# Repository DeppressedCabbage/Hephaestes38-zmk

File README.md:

<h1 align="left">Hephaestes38</h1>

Hephaestes38 is a custom, 38 key, low profile, split unibody keyboard. I Intended it to be used with the Hands Down promethium layout, but that's really up to you! ZMK studio has also been integrated, so it's super easy to make any changes you wish. See the [writeup](https://github.com/DeppressedCabbage/Hephaestes38-zmk/blob/main/Keymap.md) on Hands Down Promethium and my specific combos/layers. I only use 3 Layers, but the firmware has a total of 5 for you to add any you like. 

****

It's programmed on a Nice!Nano for wireless functonality, as well as compatibility for a Nice!View E-paper display to keep track of layers, battery status, or whatever else suits your fancy.

***
### PCB's
All files to make your own pcb's can be found in the pcb's and cases folder. The Hepheaestes38_PCB-Gerbers.zip can be uploaded into any pcb manufacturer to get them made, and all of the kicad files are available if you want to make any edits. If you are looking for an assembled PCB, reach out to me at conturakeyboards@gmail.com. A website will be coming soon if you would like to purchase pcb's or fully assembled keyboards. Stay tuned. 

***
### BOM

Additionally, you'll also need the following

- 38x SMD diodes (1N4148W)
- 38x Kailh Choc Hotswap Sockets
- 38x Kailh Choc V1 Switches
- 1x Nice!Nano
- 2× Pair of headers and sockets for the N!N (I used the easy solder machine headers, but mil-max sockets will work just fine too)
- (optional) 1x Nice!View
- (optional) 1x Lipo battery (301230)
- (optional) 1x Power switch (PCM12)
- (optional) 1x Reset switch (PTS526)
- (optional) Rubber feet to stop the keyboard sliding around (I used 3mm by 10mm ones, but if you aren't using a case it shouldn't matter much)

***
### Firmware

Hepheaestes38 runs ZMK, you can modify and compile you're own firmware by cloning the repo and making any edits you like. 

*** 
### V1 Case

This is the first version of they keyboard, and I forgot to add mounting holes to the pcb to facilitate Case attachement. I worked around this in a less than elegant way, and if you want to make v1 you would have to do something similar. Pictures are below. 

### V2 Case

Version 2 of the pcb and case are currently in progress, please follow for updates coming soon. In the meantime, here are some renders for your viewing pleasure. 

***
### To Do List

- ✔Create Case
- ✔Add via's to the pcb to facilitate Case attachement
- ✔Refine Pcb to allow for diode attachment on both sides, along with turning Diode Footprint around
- Lower profile?
- ✔ Add zmk Studio support
- Order V2 pcb's to confirm fitment

***
### Credits

This is my first foray into making my own keyboard, so special thanks go out to the entire ergo community, notably 

- [FlatFootFox](https://twitter.com/flatfootfox) - for the guide to ergogen
- [Ceoloide](https://github.com/ceoloide) - For the footprints used in creating the pcb
- [Lesshonor](https://github.com/lesshonor) - For helping me out with the getting the display to work
- And my lovely offline support system for moral support and encouragement.

***

## LICENSING
<picture align="left">
  
</picture>

This work is licensed under a
Creative Commons (4.0 International License)
Attribution—Noncommercial—Share Alike

- ✖ | Sharing without ATTRIBUTION
- ✔ | Remix Culture allowed
- ✖ | Commercial Use
- ✖ | Free Cultural Works
- ✖ | Meets Open Definition

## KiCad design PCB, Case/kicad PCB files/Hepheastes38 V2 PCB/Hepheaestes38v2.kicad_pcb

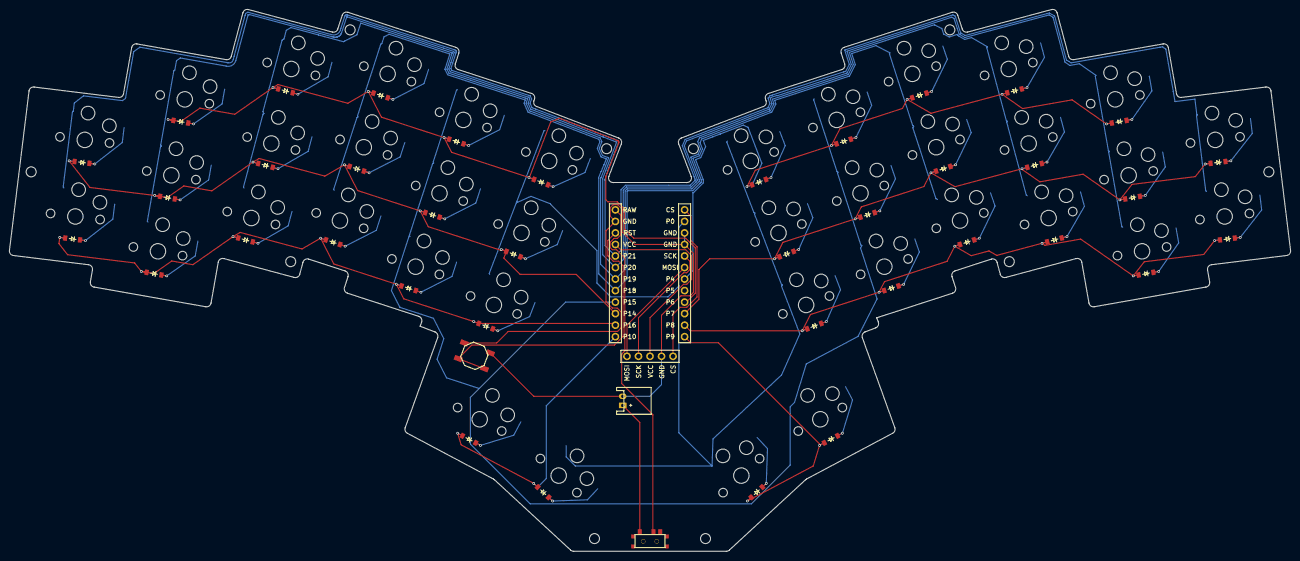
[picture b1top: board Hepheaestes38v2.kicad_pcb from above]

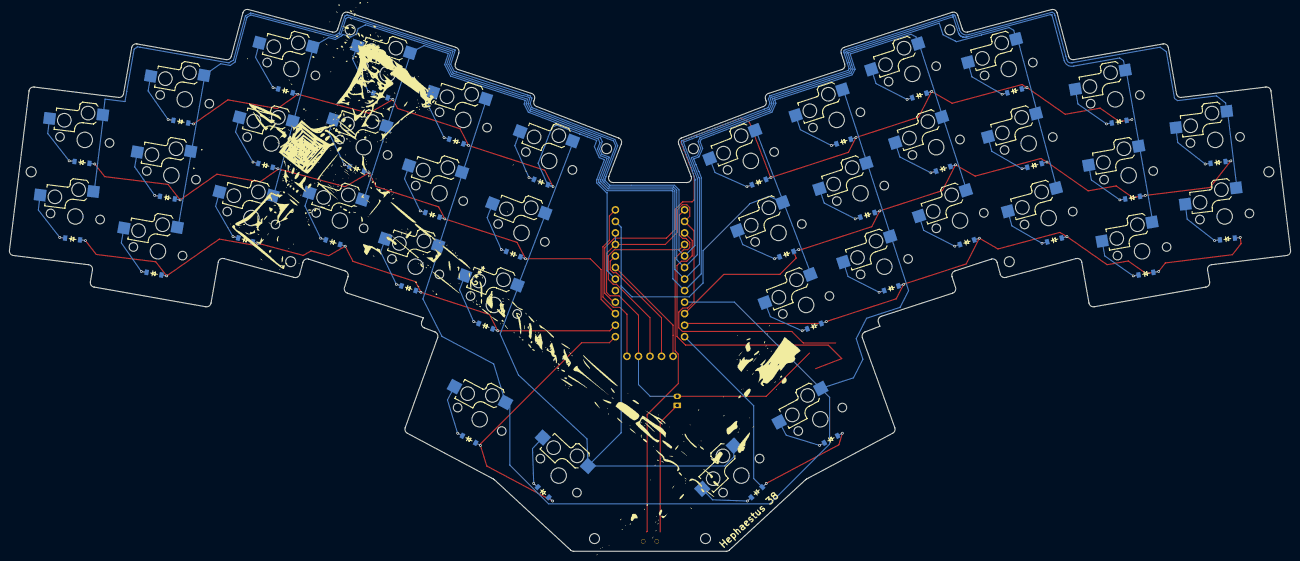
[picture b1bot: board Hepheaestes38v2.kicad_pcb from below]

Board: 2 copper layers, 282.3 x 119.4 mm, 91 parts (38 on the bottom side), 60 nets.

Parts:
B1: SW_TACT_ALPS_SKQGABE010
D1, D2, D3, D4, D5, D6, D7, D8, D9, D10, D11, D12, D13, D14, D15, D16, D17, D18, D19, D20, D21, D22, D23, D24, D25, D26, D27, D28, D29, D30, D31, D32, D33, D34, D35, D36, D37, D38: diode_tht_sod123
DISP1: display_nice_view
JST1: JST_PH_S2B-PH-K_02x2.00mm_Angled
MCU1: mcu_nice_nano
MH1, MH2, MH3, MH4, MH5, MH6, MH7, MH8, MH9, MH10: mounting_hole_npth
S1, S2, S3, S4, S5, S6, S7, S8, S9, S10, S11, S12, S13, S14, S15, S16, S17, S18, S19, S20, S21, S22, S23, S24, S25, S26, S27, S28, S29, S30, S31, S32, S33, S34, S35, S36, S37, S38: switch_choc_v1_v2
T1: SPDT_C128955

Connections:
CS: DISP1.5, MCU1.1
GND: B1.1, DISP1.4, JST1.2, MCU1.3, MCU1.4, MCU1.23
MOSI: DISP1.1, MCU1.6
P0: MCU1.2, S15.1, S16.1, S17.1, S32.1, S33.1, S34.1, S36.1, S38.1
P4: D22.2, D25.2, D28.2, D31.2, D34.2, MCU1.7
P6: D5.2, D8.2, D11.2, D14.2, D17.2, MCU1.9
P7: D19.2, D21.2, D24.2, D27.2, D30.2, D33.2, MCU1.10
P8: D18.2, D20.2, D23.2, D26.2, D29.2, D32.2, MCU1.11
P9: D37.2, D38.2, MCU1.12
P10: D35.2, D36.2, MCU1.13
P14: D2.2, D4.2, D7.2, D10.2, D13.2, D16.2, MCU1.15
P15: MCU1.16, S12.1, S13.1, S14.1, S29.1, S30.1, S31.1, S35.1, S37.1
P16: D1.2, D3.2, D6.2, D9.2, D12.2, D15.2, MCU1.14
P18: MCU1.17, S9.1, S10.1, S11.1, S26.1, S27.1, S28.1
P19: MCU1.18, S6.1, S7.1, S8.1, S23.1, S24.1, S25.1
P20: MCU1.19, S3.1, S4.1, S5.1, S20.1, S21.1, S22.1
P21: MCU1.20, S1.1, S2.1, S18.1, S19.1
RAW: MCU1.24, T1.2
RST: B1.2, MCU1.22
SCK: DISP1.2, MCU1.5
VCC: DISP1.3, MCU1.21
index_bottom: D12.1, S12.2
index_home: D13.1, S13.2
index_top: D14.1, S14.2
inner_bottom: D15.1, S15.2
inner_home: D16.1, S16.2
inner_top: D17.1, S17.2
middle_bottom: D9.1, S9.2
middle_home: D10.1, S10.2
middle_top: D11.1, S11.2
mirror_index_bottom: D29.1, S29.2
mirror_index_home: D30.1, S30.2
mirror_index_top: D31.1, S31.2
mirror_inner_bottom: D32.1, S32.2
mirror_inner_home: D33.1, S33.2
mirror_inner_top: D34.1, S34.2
mirror_middle_bottom: D26.1, S26.2
mirror_middle_home: D27.1, S27.2
mirror_middle_top: D28.1, S28.2
mirror_outer_bottom: D18.1, S18.2
mirror_outer_home: D19.1, S19.2
mirror_pinky_bottom: D20.1, S20.2
mirror_pinky_home: D21.1, S21.2
mirror_pinky_top: D22.1, S22.2
mirror_reachy_thumbrow: D38.1, S38.2
mirror_ring_bottom: D23.1, S23.2
mirror_ring_home: D24.1, S24.2
mirror_ring_top: D25.1, S25.2
mirror_tucky_thumbrow: D37.1, S37.2
outer_bottom: D1.1, S1.2
outer_home: D2.1, S2.2
pinky_bottom: D3.1, S3.2
pinky_home: D4.1, S4.2
pinky_top: D5.1, S5.2
pos: JST1.1, T1.1
reachy_thumbrow: D36.1, S36.2
ring_bottom: D6.1, S6.2
ring_home: D7.1, S7.2
ring_top: D8.1, S8.2
tucky_thumbrow: D35.1, S35.2

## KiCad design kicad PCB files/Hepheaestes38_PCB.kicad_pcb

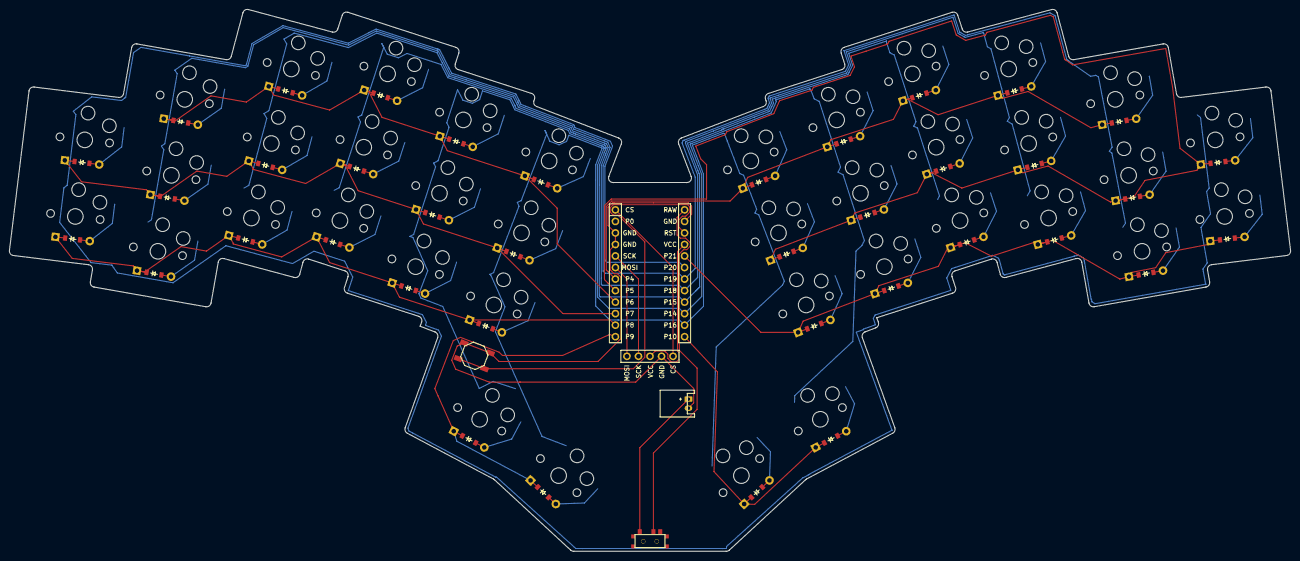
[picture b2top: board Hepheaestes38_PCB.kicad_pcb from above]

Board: 2 copper layers, 282.3 x 119.4 mm, 81 parts (0 on the bottom side), 60 nets.

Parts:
B1: SW_TACT_ALPS_SKQGABE010
D1, D2, D3, D4, D5, D6, D7, D8, D9, D10, D11, D12, D13, D14, D15, D16, D17, D18, D19, D20, D21, D22, D23, D24, D25, D26, D27, D28, D29, D30, D31, D32, D33, D34, D35, D36, D37, D38: ComboDiode
DISP1: display_nice_view
JST1: JST_PH_S2B-PH-K_02x2.00mm_Angled
MCU1: mcu_nice_nano
S1, S2, S3, S4, S5, S6, S7, S8, S9, S10, S11, S12, S13, S14, S15, S16, S17, S18, S19, S20, S21, S22, S23, S24, S25, S26, S27, S28, S29, S30, S31, S32, S33, S34, S35, S36, S37, S38: PG1350
T1: SPDT_C128955

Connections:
CS: DISP1.5, MCU1.24
GND: B1.1, DISP1.4, JST1.2, MCU1.2, MCU1.21, MCU1.22
MOSI: DISP1.1, MCU1.19
P4: D22.1, D25.1, D28.1, D31.1, D34.1, MCU1.18
P5: D19.1, D21.1, D24.1, D27.1, D30.1, D33.1, MCU1.17
P6: D5.1, D8.1, D11.1, D14.1, D17.1, MCU1.16
P7: D2.1, D4.1, D7.1, D10.1, D13.1, D16.1, MCU1.15
P8: D1.1, D3.1, D6.1, D9.1, D12.1, D15.1, MCU1.14
P9: D35.1, D36.1, MCU1.13
P10: D37.1, D38.1, MCU1.12
P14: MCU1.10, S12.1, S13.1, S14.1, S29.1, S30.1, S31.1, S35.1, S37.1
P15: MCU1.9, S9.1, S10.1, S11.1, S26.1, S27.1, S28.1
P16: MCU1.11, S15.1, S16.1, S17.1, S32.1, S33.1, S34.1, S36.1, S38.1
P18: MCU1.8, S6.1, S7.1, S8.1, S23.1, S24.1, S25.1
P19: MCU1.7, S3.1, S4.1, S5.1, S20.1, S21.1, S22.1
P20: MCU1.6, S1.1, S2.1, S18.1, S19.1
P21: D18.1, D20.1, D23.1, D26.1, D29.1, D32.1, MCU1.5
RAW: MCU1.1, T1.2
RST: B1.2, MCU1.3
SCK: DISP1.2, MCU1.20
VCC: DISP1.3, MCU1.4
index_bottom: D12.2, S12.2
index_home: D13.2, S13.2
index_top: D14.2, S14.2
inner_bottom: D15.2, S15.2
inner_home: D16.2, S16.2
inner_top: D17.2, S17.2
middle_bottom: D9.2, S9.2
middle_home: D10.2, S10.2
middle_top: D11.2, S11.2
mirror_index_bottom: D29.2, S29.2
mirror_index_home: D30.2, S30.2
mirror_index_top: D31.2, S31.2
mirror_inner_bottom: D32.2, S32.2
mirror_inner_home: D33.2, S33.2
mirror_inner_top: D34.2, S34.2
mirror_middle_bottom: D26.2, S26.2
mirror_middle_home: D27.2, S27.2
mirror_middle_top: D28.2, S28.2
mirror_outer_bottom: D18.2, S18.2
mirror_outer_home: D19.2, S19.2
mirror_pinky_bottom: D20.2, S20.2
mirror_pinky_home: D21.2, S21.2
mirror_pinky_top: D22.2, S22.2
mirror_reachy_thumbrow: D38.2, S38.2
mirror_ring_bottom: D23.2, S23.2
mirror_ring_home: D24.2, S24.2
mirror_ring_top: D25.2, S25.2
mirror_tucky_thumbrow: D37.2, S37.2
outer_bottom: D1.2, S1.2
outer_home: D2.2, S2.2
pinky_bottom: D3.2, S3.2
pinky_home: D4.2, S4.2
pinky_top: D5.2, S5.2
pos: JST1.1, T1.1
reachy_thumbrow: D36.2, S36.2
ring_bottom: D6.2, S6.2
ring_home: D7.2, S7.2
ring_top: D8.2, S8.2
tucky_thumbrow: D35.2, S35.2

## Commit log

2025-03-21 Updated Build.yml
2025-03-21 Forgot Keymap file, added.
2025-03-22 Fixed typo in include files for my overlay
2025-03-22 Reformatted matrix transform
2025-03-22 Fixed Typo in keymap
2025-03-22 removed kscan node in overlay
2025-03-22 Changed formatting in defconfig
2025-03-22 Set gpio row2col
2025-03-22 Fixed typo in overlay
2025-03-22 Reorganizing matrix tranform
2025-03-22 fixed pin callouts
2025-03-22 Added nav layer
2025-03-22 Nav layer typo
2025-03-22 Added combos
2025-03-22 fixed combo typo
2025-03-22 Removed layer filters on combos
2025-03-22 Added escape and enter combos
2025-03-22 Redefined escape and enter keys
2025-03-22 Added missing key in num layer
2025-03-22 Corrected combo key defines
2025-03-22 Changed @ callout, added right arrow key, fixed pg down
2025-03-23 Added windows and delete combos
2025-03-23 Adjusted windows combo position
2025-03-24 Added quick release to sticky key, moved delete combo position
2025-03-24 Reformatted sticky key config
2025-04-03 added kicad pcb files
2025-04-03 General organisation
2025-04-05 Added PCB Gerber Files
2025-04-10 added nice view sheild
2025-04-10 removed Nice View Adapter
2025-04-10 Turned on external power
2025-04-10 added external power in kconfig
2025-04-10 added compatible in ext power management
2025-04-10 fixed typo
2025-04-11 fixed external power callout
2025-04-11 changed pin layout
2025-04-18 Rename boards/shields/Hephaestes38/Kconfig.conf to boards/shields/Hephaestes38.conf
2025-04-18 Rename boards/shields/Hephaestes38.conf to boards/shields/Hephaestes38/Hephaestes38.conf
2025-04-19 Configured Custom Spi node for Nice!View
2025-04-19 Reorginized File structure
2025-04-19 Added bluetooth profiles to keymap
2025-04-19 removed display commands in .conf
2025-04-19 refined keymap
2025-04-20 Added zmk studio support
2025-04-20 Moved Physical Layout to new file, added hardware metadata
2025-04-20 Renamed physical Layout dtsi
2025-04-20 Updated pathing for layouts.dtsi
2025-04-20 Added reserved layers
2025-04-20 Used Relative path for dtsi
2025-04-20 Moved physical layout back to overlay, added usb uart capability
2025-04-20 Added studio unlock to keymap
2025-04-20 Re-pathing layout.dtsi again
2025-04-20 Reformatted layout.dtsi pathing
2025-04-20 Removed chosen matrix tranform, replaced with chosen physical layout
2025-04-20 Added Studio to hardware Metadata!!!
2025-04-20 Show battery status as percentage instead of icon
2025-04-20 Updated to nice view gem
2025-04-20 Added layer names
2025-04-20 Added battery reporting in kconfig
2025-04-20 Added battery sensor driver in overlay
2025-04-20 Reformatted device tree
2025-04-20 fixed typo in device tree
2025-04-26 Updated Folder Structure, cleaned up case files
2025-04-27 Rotated Diodes so silkscreen shows correct orientation
2025-04-27 Update README.md to include pictures of the case
2025-05-02 Fixed typo in Hephaestes38.keymap
2025-11-22 Update Hephaestes38v2.yml
    Moved some of the mounting holes, updated yaml
2025-11-22 uploading new v2 pcb files
2025-11-22 Re-organised folder structure, adding v2 CAD
2025-11-23 Updating V2 Case files
2025-11-24 updating revised v2 case parts
2025-11-24 added keymap file for the keymap editor
2025-11-24 added layout information to config directory
2025-11-24 One more time
2025-11-24 Removed all of that stuff because I don't want to deal with it right now
2025-12-03 Added pictures to keymap
2025-12-03 Update build.yaml
    Changed Nice!Nano version to be V2 from V1
2025-12-04 Added QWERTY Layer to keymap
    Layer 4 is now a QWERTY Layer instead of the previous blank reserved layer.
2025-12-04 Update Hephaestes38.keymap
    Fixing key positions on the qwerty layer
2025-12-04 Update Hephaestes38.keymap
    I forgot "B", added
2025-12-04 Added details to Keymap.md
    Added much more details to the keymap writeup, including the qwerty layer.
2025-12-11 Update build.yaml
    Fix For breaking zmk changes
2025-12-13 Updating Case Components
2025-12-13 Reorignized file structure
2025-12-13 fix typo in README.md
2025-12-13 Update west.yml
    Changing Nice!View Overlay to forked repository
2025-12-13 Update west.yml
    Pinned ZMK Version To avoid breaking Changes
2025-12-20 Revised PCBv2 Gerber And files
2025-12-20 Made changes to the case files
2025-12-26 added bluetooth clear profile key
2025-12-26 enabled bluetooth expiramental features to help with connectivity issues
